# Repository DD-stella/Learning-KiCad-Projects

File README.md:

# Learning-KiCad-Projects
你好！我是 柯宇鴻，這是用來記錄我從零開始學習 KiCad PCB 設計的 GitHub 倉庫。
我希望藉由實作不同的專案，掌握電路圖設計與 PCB 佈線的技能，為未來的專案打下基礎。

## 🎯 KiCad 硬體開發標準 SOP 學習目標✅

為了掌握系統化的硬體電路設計流程，我將依據標準 SOP 逐步完成以下階段的學習與實作：

### 1. 原理圖設計 (Schematic Capture) 
- ✅ 掌握元件庫搜尋與基本元件放置（R, C, IC, Connector）
  > 實作筆記：
  > 1. 按下快捷鍵'A'可以搜尋並新增符號
  > 2. 將滑鼠移到元件上，按'R'可以旋轉方向、按'M'可以移動。
  > 3. 按下快捷鍵'W'可以畫綠色的導線(其實也可以不用按)連接元件接腳，按'Esc'退出。
  
- ✅ 理解並正確放置「電源標籤」(Power Flag) 解決電源供應端判定問題
  > 實作筆記：
  > 1. ★★★ 雖然在電路圖中放了'+5' 和 'GND'，但 KiCad 預設不知道電源是從哪裡「輸入」的，因此直接執行 ERC 會報錯。
  > 2. ★★★ 解決方法：按 'A' 搜尋 'PWR_FLAG'（電源標籤）並放置兩個。
  > 3. 將其中一個接在 '+5V'和'GND'線路上，藉此告訴系統這兩條是電源源頭。

- ✅ 執行原理圖「電氣規則檢查」(ERC) 並修正所有 Errors 與 Warnings
  > 實作筆記：
  > 1. 點選上方工具列的圖示(ERC)開啟檢查視窗。
  > 2. 點擊「執行 ERC」，只要「違規」頁籤顯示為 **(0)** 即代表完全通過。

### 2. 元件庫管理與自建元件 (Library Management)
- ✅ 學會閱讀晶片數據手冊 (Datasheet)，理解引腳定義與電氣屬性
  > 實作筆記：
  > 1. 畫晶片的第一步絕對是查 Datasheet 確認引腳功能(例如 NE555 讓 LED 閃爍的電路中，Pin 1 是 GND、Pin 8 是 VCC、Pin 3 是 OUT)。
  > 2. ★★★ 註：如果要參考 Datasheet 的詳細設計與封裝規範，請以 [HackMD 講義](https://hackmd.io/@Ethan2339/S1SOPAPhC) 網站裡的標準為主。

- ✅ 實作「自建電路圖符號」(Custom Symbol)，手動繪製晶片符號並設定 Pin Type (Input/Output/Power)
  > 實作筆記：
  > 1. 建立新圖庫並在「管理符號庫」掛載時，路徑一定要選 `${KIPRJMOD}` 開頭的「相對路徑」！
  > 2. ★★★ 如果留著 `C:\...` 開頭的絕對路徑，換台電腦或上傳 GitHub 後，系統會去別人的 C 槽找檔案，絕對會大翻車「查無此零件」，而且系統也會查不到。
  > 3. ★★★在畫晶片接腳(按 'P')時，端點小圓圈要朝外(那是用來接線的)。
  > 4. 「電氣類型」一定要照 Datasheet 乖乖選（例如 VCC 和 GND 要選 Power Input）。亂選的話，畫完電路圖按 ERC 會被錯誤訊息淹沒。
- ✅ 實作「自建封裝」(Custom Footprint)，根據 Datasheet 尺寸精密計算焊盤 (Pad) 大小、間距 (Pitch) 與邊界線 (Courtyard)
  > 實作筆記：
  > 1. 建立封裝庫一樣要選 '專案(Project)' 層級，確保上傳 GitHub 後路徑不會出錯。
  > 2. ★★★ 尺寸計算與格點設定：DIP-8 封裝的引腳間距 (Pitch) 是 2.54mm (100 mil)，左右排間距是 7.62mm (300 mil)。可以直接把上方選單的格點改為 '2.5400 mm (100.00 mils)'。這樣放置下一個焊盤時，只要相差一格，距離就絕對精準！
  > 3. ★★★ 焊盤(Pad)擺放與編號規則：點選右側的黃色圓圈圖示(加入焊盤)開始打洞
  > 4. ★★★ 第一腳防呆設定：滑鼠指著 Pin 1 按鍵盤'E'編輯，將形狀改成'矩形' (其餘 2-8 腳保持圓形)。並在 'F.Silkscreen'(絲印層)用圓形工具畫個小圓點在 Pin 1 旁邊。
  > 5. 外框與邊界設計：在 'F.Silkscreen' 用矩形工具畫個框包住 8 個腳；接著★★★ 絕對不能忘記切換到 'F.Courtyard'(邊界線)再畫一個更大的隱形外框！這是零件的防撞結界，沒畫的話 DRC 無法進行碰撞檢查，到時候跟其他零件擠在一起工廠會拒絕生產。

### 3. 電路板佈線 (PCB Layout)
- ✅ 將原理圖設計正確導入 PCB 編輯器中
  > 實作筆記：
  > 1. 在原理圖中按下快捷鍵 'F8' 就可以把零件實體化傳送到 PCB 世界。
  > 2. 剛傳過去時零件會黏在滑鼠上，在畫面點一下左鍵就可以把它們放出來。

- ✅ 在 `Edge.Cuts` 層定義精確的電路板尺寸與板框
  > 實作筆記：
  > 1. ★★★ 畫板框前，右邊圖層一定要切換到 'Edge.Cuts' 層（通常是黃色的）。如果用別層畫，工廠會不知道從哪裡切板子！
  > 2. 選好圖層後，使用右側的「繪製矩形」工具在零件周圍畫一個框，這就是板子的邊界(點兩下可以修改長寬)。

- ✅ 設定符合生產工廠規範的「設計規則」(Constraints / Design Rules)
  > 實作筆記：
  > 1. 預設的 '0.2mm' 線寬太細了，工廠做出來可能會斷掉。
  > 2. ★★★ 解決方法：在左上角線寬選單點選「編輯預定義尺寸」，新增一個 '0.4mm' 尺寸並選用它。

- ✅ 執行「設計規則檢查」(DRC) 確保板子無任何短路、斷路或間距衝突
  > 實作筆記：
  > 1. 按下快捷鍵'X'可以開始拉線(F.Cu紅色的那一層)。
  > 2. ★★★ 把所有白色的飛線都拉成紅色的實體導線後，點擊上方圖示(ERC)執行檢查。
- ✅ 實作去耦電容 (Decoupling Capacitor)「盡量靠近晶片電源腳」的佈局規範
  > 實作筆記：
  > 1. ★★★ 去耦/濾波電容(如 C2)一定要貼死在晶片對應的引腳旁邊(Pin 5)！
  > 2. 這是因為高頻雜訊很敏感，只要導線拉長一點點，電容直接當場廢掉。
  > 3. 佈線時，所有的 GND 飛線通通不准用手拉。
  > 4. ★★★ 預留秘密武器：下一動要用「大面積鋪銅」，讓所有的 GND 自動接通。
- ✅ 執行「設計規則檢查」(DRC) 確保板子無任何短路、斷路或間距衝突
  > 實作筆記：
  > 1. 按下快捷鍵'X'可以開始拉線(F.Cu紅色的那一層)。
  > 2. ★★★ 把所有白色的飛線都拉成紅色的實體導線後，點擊上方圖示(ERC)執行檢查。
  > 3. 舖完銅之後，點擊上方圖示(DRC)執行檢查，只要違規與未連線項目都顯示為 **(0)** 就算完美通關！
- ✅ 透過 3D 檢視器(3D Viewer)進行機構防撞與高度驗證，並導出高解析度 3D 渲染圖
  > 實作筆記：
  > 1. 按下快捷鍵 'Alt+3' 可以開啟 3D 查看器。
  > 2. ★★★ 機構驗證重點：不只是好看，更重要的是在送去工廠前，確認電感、電容、排針實體高度會不會跟板框或外殼卡到（進行機構干涉檢查）。
- 如果有更新原圖，可以按圖是(更新PCB進行放置新元件)

↑第一個作品↑

### 4. 生產製造輸出 (Manufacturing & DFM)
- ✅ 導出符合工廠打樣標準的 Gerber 光繪檔與鑽孔檔 (Drill files)
  > 實作筆記：
  > 1. ★★★ 導出路徑建議：不要直接丟在專案根目錄，新建一個叫 'Gerber' 的資料夾來放，不然上百個製造檔會把 GitHub 塞爆。
  > 2. 在 PCB 編輯器點選「檔案」->「製造輸出」->「Gerber」，勾選必備圖層 (F.Cu、B.Cu、F.Silkscreen、B.Silkscreen、F.Mask、B.Mask、Edge.Cuts)。
  > 3. 點選「繪製(Plot)」生成光繪檔；接著點選「產生鑽孔檔」生成孔位數據，缺一不可！

- ✅ 使用 Gerber 查看器 (Gerber Viewer) 進行出廠前自主檢查
  > 實作筆記：
  > 1. 這是 DFM(可製造性設計)的精髓。在送交工廠前，必須用 KiCad 主畫面的 'Gerber 查看器' 開啟剛導出的所有檔案。
  > 2. ★★★ 自檢重點：確認文字(Silkscreen)有沒有疊在焊盤上、孔位(Drill)有沒有偏心、板框(Edge.Cuts)是不是閉合的。

- ✅ 輸出完整的物料清單 (BOM 表)
  > 實作筆記：
  > 1. BOM 表就是零件採購清單。
  > 2. 在原理圖編輯器點選「工具」->「產生 BOM」，導出一個 CSV 格式的檔案。
  > 3. ★★★ 採購核對重點：確認元件的阻值、容值、封裝規格(如 DIP-8)都有寫清楚，到時候去電子材料行買零件才不會買錯。

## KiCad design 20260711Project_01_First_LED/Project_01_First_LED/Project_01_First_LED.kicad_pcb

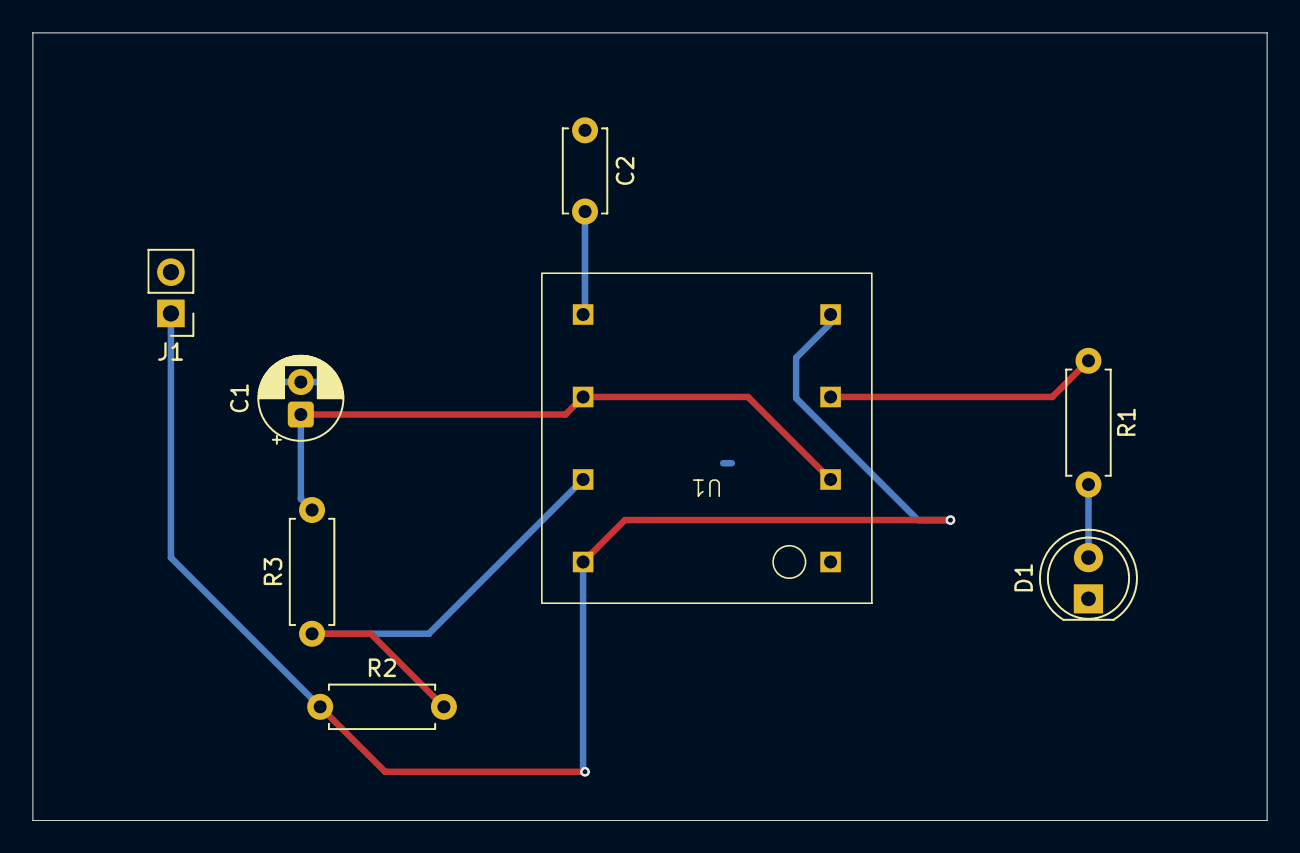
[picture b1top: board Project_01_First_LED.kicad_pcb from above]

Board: 2 copper layers, 76.0 x 48.5 mm, 8 parts (0 on the bottom side), 7 nets.

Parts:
C1: 10uF; CP_Radial_D5.0mm_P2.00mm
C2: 0.1uF; C_Disc_D5.0mm_W2.5mm_P5.00mm
D1: LED; LED_D5.0mm
J1: Conn_01x02_Pin; PinHeader_1x02_P2.54mm_Vertical
R1: 220; R_Axial_DIN0207_L6.3mm_D2.5mm_P7.62mm_Horizontal
R2: 1k; R_Axial_DIN0207_L6.3mm_D2.5mm_P7.62mm_Horizontal
R3: 10k; R_Axial_DIN0207_L6.3mm_D2.5mm_P7.62mm_Horizontal
U1: MY_DIP-8

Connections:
+5V: J1.1, R2.1, U1.4 (RESET), U1.8 (VCC)
GND: C1.2, C2.1, D1.1 (K), J1.2, U1.1 (GND)
unnamed: D1.2 (A), R1.2
unnamed: C2.2, U1.5 (CONT)
unnamed: R2.2, R3.1, U1.7 (DISCH)
unnamed: R1.1, U1.3 (OUT)
unnamed: C1.1, R3.2, U1.2 (TRIG), U1.6 (THRES)
